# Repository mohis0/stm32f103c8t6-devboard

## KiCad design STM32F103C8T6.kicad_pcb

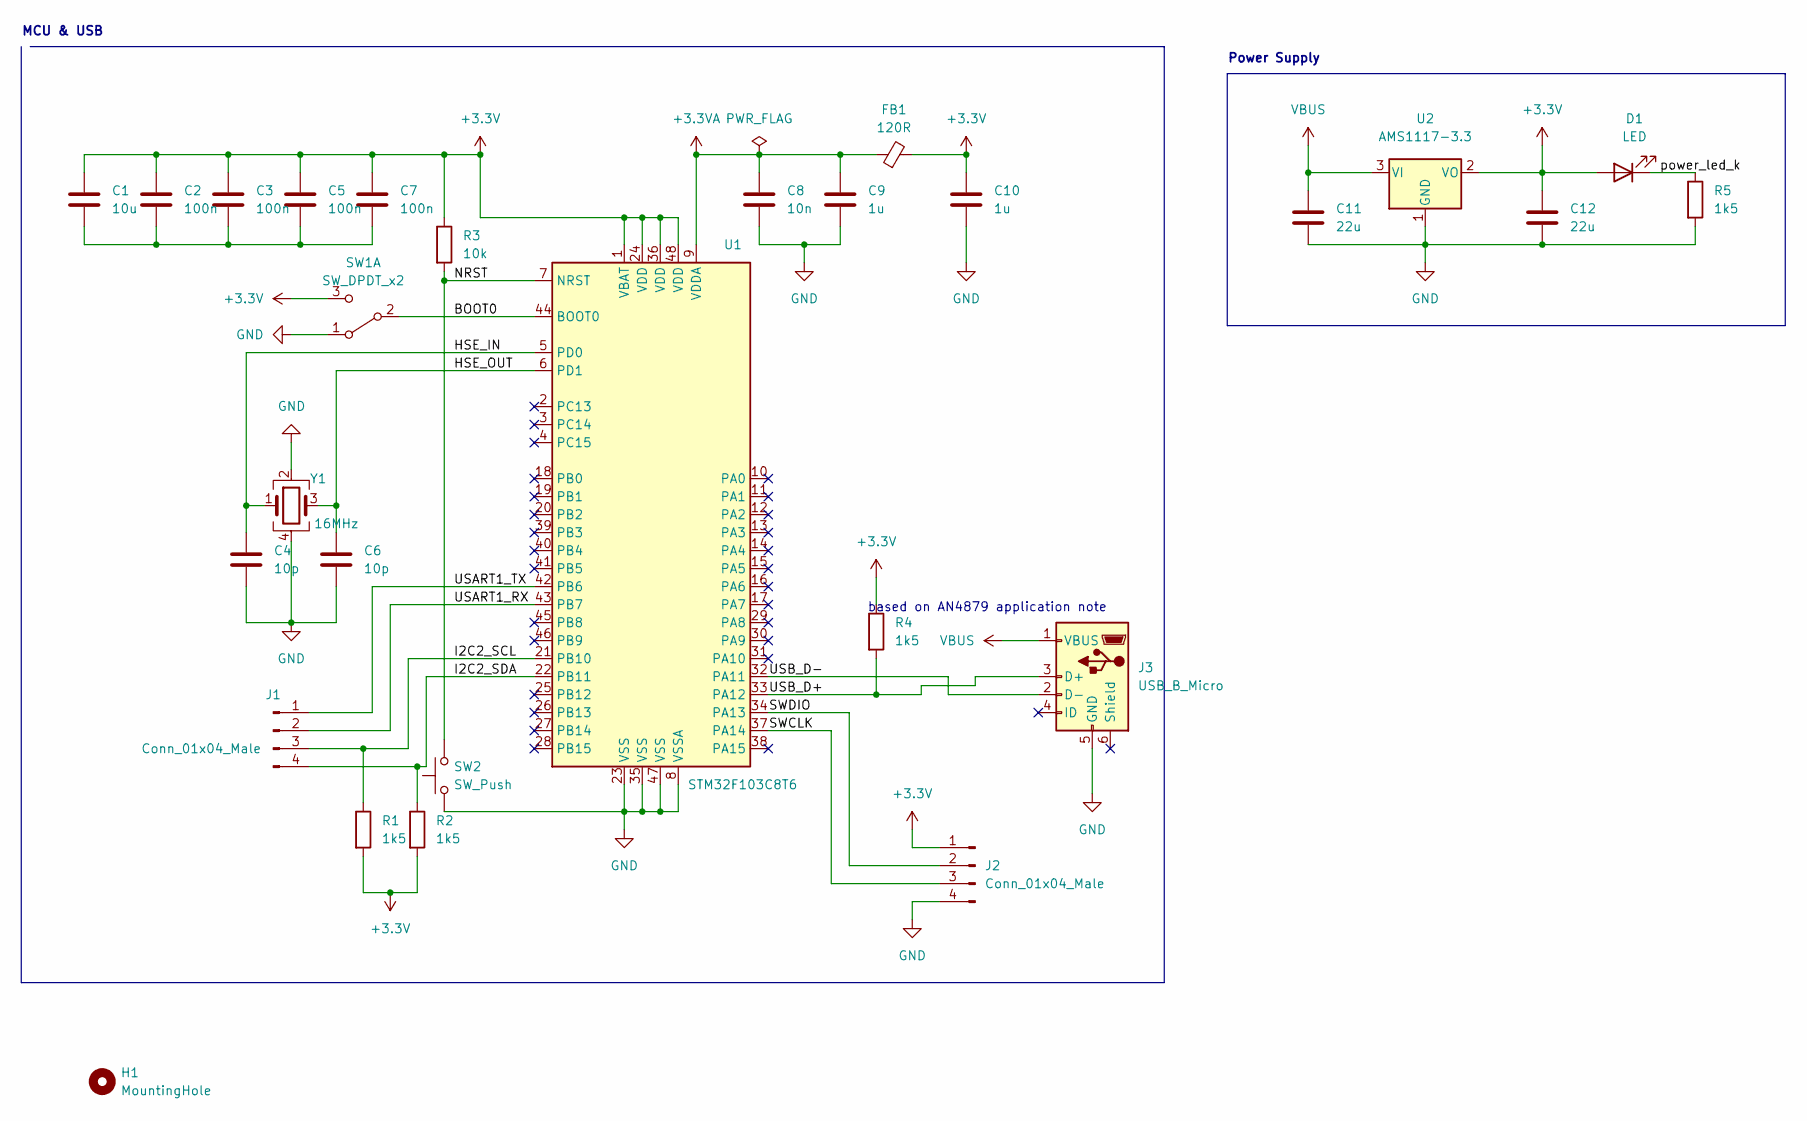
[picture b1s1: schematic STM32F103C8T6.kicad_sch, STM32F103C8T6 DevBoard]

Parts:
C1: 10u; C_0805_2012Metric
C2, C3, C5, C7: 100n; C_0805_2012Metric
C4, C6: 10p; C_0805_2012Metric
C8: 10n; C_0805_2012Metric
C9, C10: 1u; C_0805_2012Metric
C11, C12: 22u; C_0805_2012Metric
D1: LED; LED_0805_2012Metric
FB1: 120R; L_0805_2012Metric
H1: MountingHole; MountingHole_2.2mm_M2
J1, J2: Conn_01x04_Male; PinHeader_1x04_P2.00mm_Vertical
J3: USB_B_Micro; USB_Micro-B_Wuerth_629105150521
R1, R2, R4, R5: 1k5; R_0805_2012Metric
R3: 10k; R_0805_2012Metric
SW1: SW_DPDT_x2; SW_SPDT_PCM12
SW2: SW_Push; SW_PUSH_6mm
U1: STM32F103C8T6; LQFP-48_7x7mm_P0.5mm
U2: AMS1117-3.3; SOT-223-3_TabPin2
Y1: 16MHz; Crystal_SMD_3225-4Pin_3.2x2.5mm

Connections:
+3.3VA: C8.1, C9.1, FB1.1, U1.9 (VDDA)
+3V3: C1.1, C2.1, C3.1, C5.1, C7.1, C10.1, C12.1, D1.2 (A), FB1.2, J2.1, R1.2, R2.2, R3.1, R4.1, SW1.3 (C), U1.1 (VBAT), U1.24 (VDD), U1.36 (VDD), U1.48 (VDD), U2.2 (VO)
/BOOT0: SW1.2 (B), U1.44 (BOOT0)
/HSE_IN: C4.1, U1.5 (PD0), Y1.1
/HSE_OUT: C6.1, U1.6 (PD1), Y1.3
/I2C2_SCL: J1.3, R1.1, U1.21 (PB10)
/I2C2_SDA: J1.4, R2.1, U1.22 (PB11)
/NRST: R3.2, SW2.2, U1.7 (NRST)
/SWCLK: J2.3, U1.37 (PA14)
/SWDIO: J2.2, U1.34 (PA13)
/USART1_RX: J1.2, U1.43 (PB7)
/USART1_TX: J1.1, U1.42 (PB6)
/USB_D+: J3.3 (D+), R4.2, U1.33 (PA12)
/USB_D-: J3.2 (D-), U1.32 (PA11)
/power_led_k: D1.1 (K), R5.1
GND: C4.2, C6.2, C8.2, C9.2, C10.2, C11.2, C12.2, J2.4, J3.5 (GND), R5.2, SW1.1 (A), SW2.1, U1.8 (VSSA), U1.23 (VSS), U1.35 (VSS), U1.47 (VSS), U2.1 (GND), Y1.2, Y1.4
unnamed: C1.2, C2.2, C3.2, C5.2, C7.2
VBUS: C11.1, J3.1 (VBUS), U2.3 (VI)

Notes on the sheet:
based on AN4879 application note
MCU & USB
Power Supply

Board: 2 copper layers, 28 parts (0 on the bottom side), 18 nets, no tracks yet.

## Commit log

2024-06-26 init
